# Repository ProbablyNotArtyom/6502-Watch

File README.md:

# 6502-Watch
6502 powered wearable with an LCD screen, keyboard interface, and compact form factor, all running ehBasic to boot.

<p align="center">
    <a href="https://hackaday.io/project/166496-65p-6502-powered-watch">(Link to this project's Hackaday.io page)</a>
    <br>
    <a href="https://blog.notartyoms-box.net/6502-watch">(Link this project's homepage on my website)</a>
</p>

### About

The 6502 has been around for just about 40 years, yet still powers the hearts of many electrical systems in place today, such as many microcontrollers and embedded systems. In fact, WDC still manufactures the 6502 and 65xx series chips under the 65c02 and 65cxx. I've noticed that WDC also introduced more package variants of the 6502 and 6522, such as PLCC and QFP. Another thing I noticed was the fact that these form factors of the 65c02 are almost never used. Given that the only people buying these are hobbyists, that isn't too suprizing, as they dont offer much over the standard 40 pin DIP.What they do offer, however, is small package size. I went off to try and design the smallest 6502 SBC i could, and was pleasantly suprized with the results. What I ended up with was what i think is the smallest hobbyist 6502 SBC produced. Small enough, in fact, that you could easily wear it on your wrist! I then added the neat little Nokia 5110 LCD and a cool interface, and now have what I believe to be the only 6502-driven watch in existance.

This repository contains all of the KiCad project files for the hardware, and all of the assembly sources for my software. To build the software you will need KickAssembler.

### Hardware

The watch is pretty standard as far as 6502 hardware goes:

 * 65c02 running @ 8MHz
 * 65c22 (controls LCD, keyboard, and buttons)
 * Nokia 5110 LCD (84x48)
 * 32k SRAM
 * 16k ROM
 * C64 Keyboard Connector

Probably the strangest bit there is the full size C64 keyboard connector along the top of the watch. I had wanted to have some form of keyboard input, but most options are entirely out of reach of the poor 6502. The only way i could come up with is to use a preexisting matrix keyboard; I happened to have a lot of unused commodore keyboards, so that's what ended up on there.

The part that ties everything together is really the tiny Nokia LCD. It's interfaced through SPI, which i had to bitbang through the 6522 VIA. The VIA also interfaces with the keyboard, and the face buttons. An interesting thing to note here is that the VIA only has 16 i/o pins, which in this case are all needed to interface just with the keyboard alone. I was able to use some of those pins for both the keyboard and the LCD without causing any sort of corruption with a bit of luck, and a lot more trial and error.

### Software

The watch has a few different things on its ROM. The primary thing is G'Mon, a machine monitor i wrote for the 6502. It  supports viewing memory in single and batch, depositing memory in single or batch, jumping to programs, filling blocks of memory with a pattern byte, and moving blocks of memory. I had to strip a few of the less useful commands out in order to fit it on the ROM with everything else. The secondary thing on there is Lee Davidson's Enhanced Basic. I was just barely able to fit into the ROM with everything else, like there are only around 100 bytes free. EhBasic has been modified to hook into the watch's main code, but other than that it's a completely normal version of EhBasic!

The thing that greets you when you start up the watch is the watch interface. Clever name, i know. It just provides a graphical menu you can move through to select what you want to run. This is the only place where the face buttons are actually used, at least on purpose. The topmost button is what brings up the menu. Interesting bit about that: its connected directly to the NMI pin on the 6502, so it can be used to get back to the watch menu from almost anywhere on the thing (unless you crash the 6502).

In my sources, there is a big blob of code that handles interfacing with the watch hardware; It's called the kernel there, but its less of a kernel and more of a library everything else references. Some of the more interesting things in there are the SPI bitbanging stuff for the LCD, and the matrix scanning and decoding routine for the keyboard.

Speaking of sources, they are all uploaded on here, of course. All the assembler code is written to be assembled using KickAssembler, and makes quite heavy use of its macro capabilities, so i doubt it would be fun to try and assemble with anything else. Here i have also included the EhBasic sources that i have modified; They have been modified to be assembled with KickAssembler. Everything builds at the same time, just run the ./Compile.sh script and it will spit out a ROM image. If for some reason you feel the need to fiddle with it, then make sure to go to Configuration.asm: That's the header that holds a bunch of the miscellaneous variables, like the location of the ROM in memory.

If you every wanted to run the software yourself, then you can do that as well. If you set the Emulated variable in the config file to true, then it will build a ROM for use with Symon.

### Other Software Toys

I have written a few extra programs to show what the hardware itself can do. The first thing is a little sprite demo that has 8 animated software sprites bouncing around the screen, plus a text scroller along the top. The visibility is quite poor with it, as the LCD sure does take its time with updating the pixels, which causes everything moving to be a little blurry. To combat this I had to wait a bit after each frame for the LCD to update, which means that the demo itself runs a little slower than it actually could on the hardware. A video of this demo in action is in the Demos section.

Did i mention it runs Tetris? Because yea, it sure does. I wrote a version of Tetris for the watch not long after realizing it was probably the only practical thing that it could feasibly do. Its a pretty standard Tetris clone, following pretty much all of the mechanics of the original versions. This means having the scoring system, having the progressive levels, all the tetrominoes, etc. Its controlled using the face buttons, using the navigation buttons as left & right, the center button as rotate, and the NMI button as the drop button. At the moment I don't have actual recordings of Tetris running on the watch, mostly because i am too lazy to do that much work for a project that was finished nearly 2 and a half years as of this write-up, but i do have the graphics assets i made for it, and have put them together into what it looks like while. If you don't believe that I wrote Tetris for it, then don't worry, just take a look at the sources that i have included with the project's main downloads.

### More Information

 * [My Website](http://notartyoms-box.net/6502watch.html)

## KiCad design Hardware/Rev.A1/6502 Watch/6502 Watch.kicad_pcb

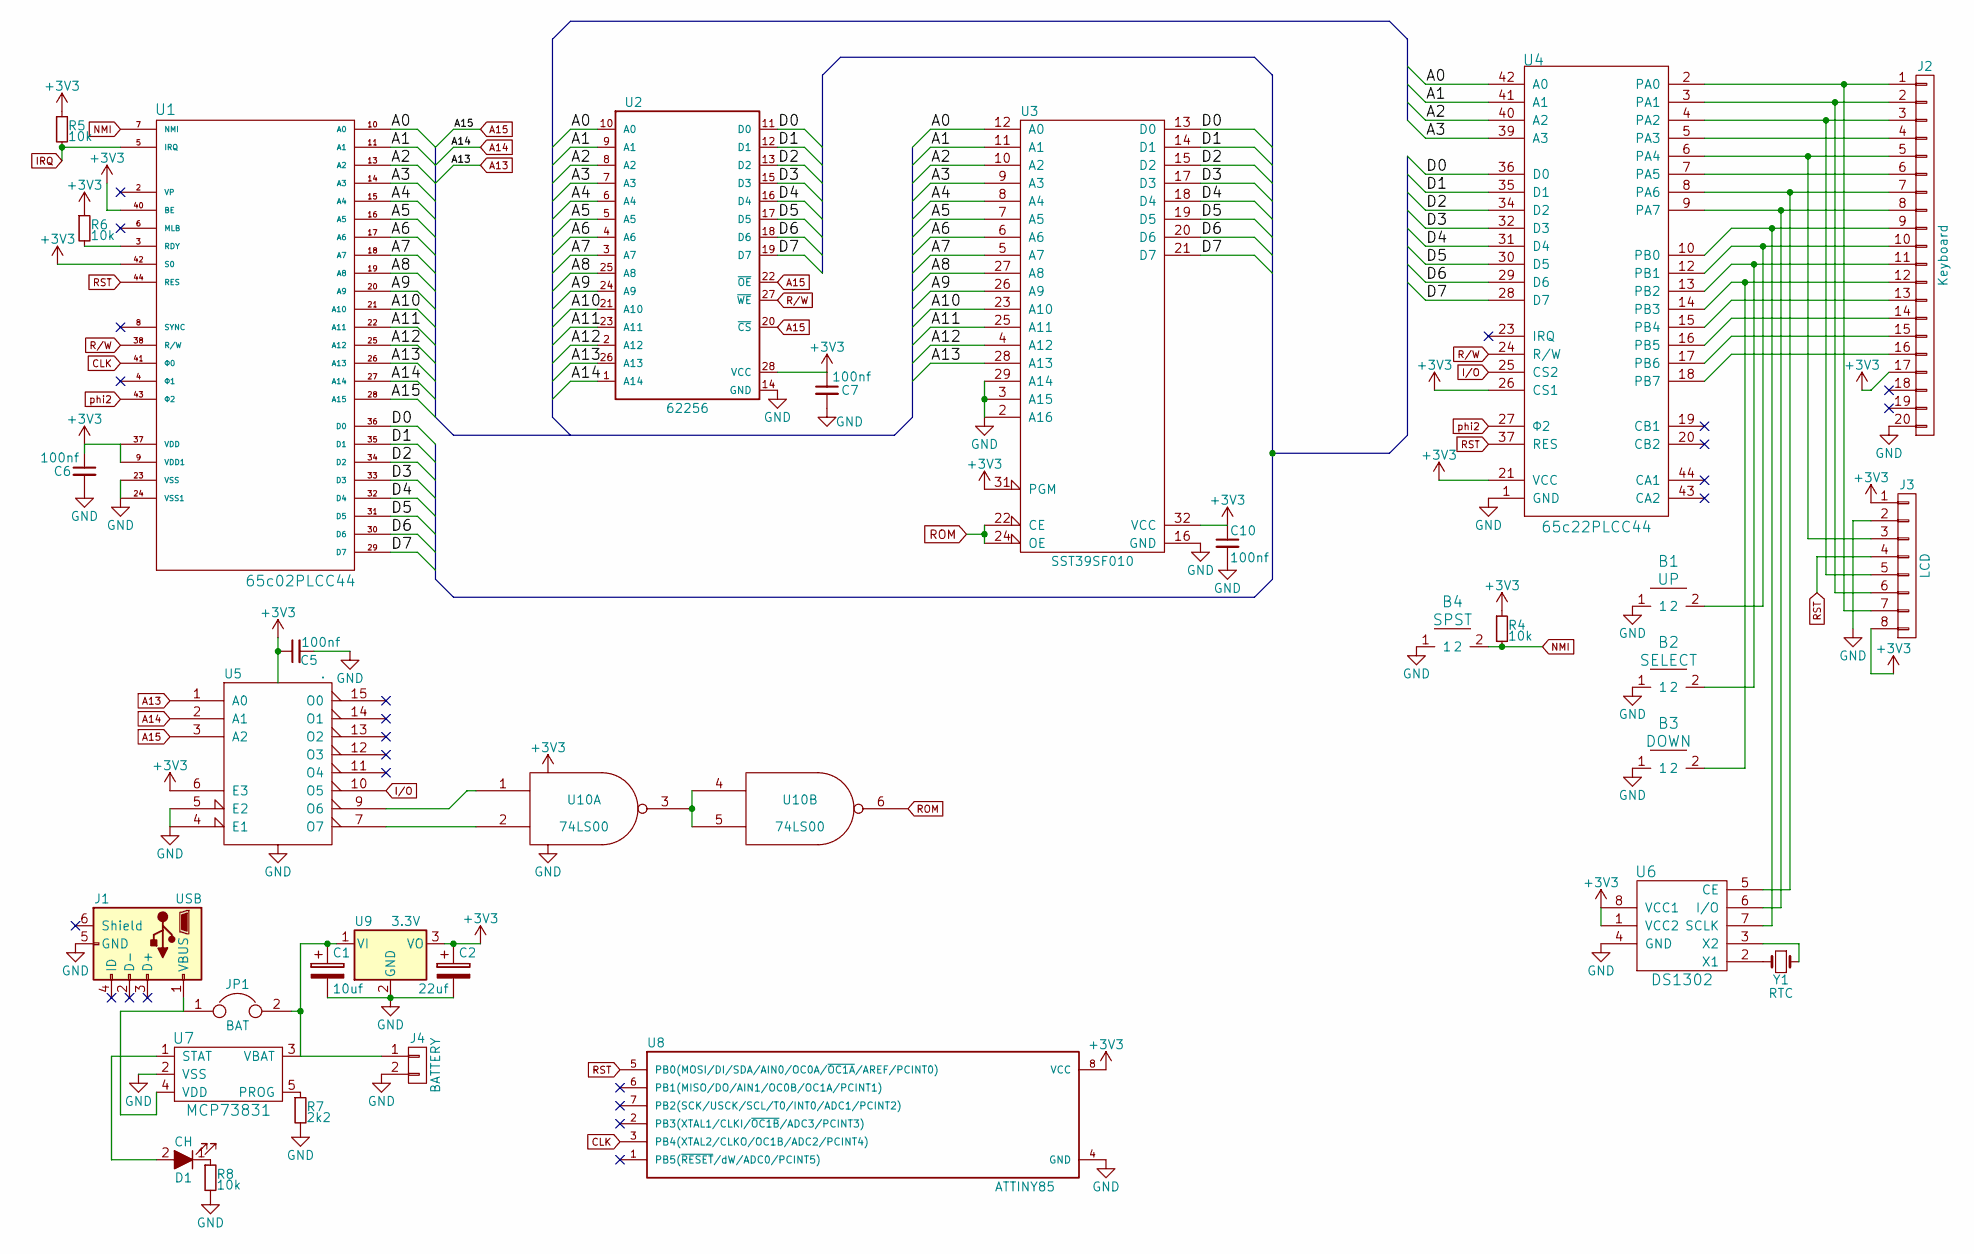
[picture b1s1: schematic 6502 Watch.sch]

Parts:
B1: UP; SW_SPST_B3S-1000(4P)
B2: SELECT; SW_SPST_B3S-1000(4P)
B3: DOWN; SW_SPST_B3S-1000(4P)
B4: SPST; SW_SPST_B3S-1000(4P)
C1: 10uf; C_1206_HandSoldering
C2: 22uf; C_1206_HandSoldering
C5, C6, C7, C10: 100nf; C_1210_HandSoldering
D1: CH; LED_1206
J1: USB; USB_Mini-B
J2: Keyboard; Pin_Header_Angled_1x20_Pitch2.54mm
J3: LCD; Pin_Header_Straight_1x08_Pitch2.54mm
J4: BATTERY; Pin_Header_Straight_1x02_Pitch2.54mm
JP1: BAT; R_0805_HandSoldering
R4, R5, R6, R8: 10k; R_1206_HandSoldering
R7: 2k2; R_1206_HandSoldering
U1: 65c02PLCC44; PLCC-44
U2: 62256; SOP-28_8.40x48mm_Pitch1.27mm
U3: SST39SF010; PLCC-32_THT-Socket_Fixed
U4: 65c22PLCC44; PLCC-44
U5: .; SOIC-16_3.9x9.9mm_Pitch1.27mm
U6: DS1302; SOIC-8_3.9x4.9mm_Pitch1.27mm
U7: MCP73831; SOT-23-5_HandSoldering
U8: ATTINY85; SOIC-8-N
U9: 3.3V; SOT-223-3Lead_TabPin2
U10: 74LS00; SOIC-14_3.9x8.7mm_Pitch1.27mm
Y1: RTC; Crystal_DS26_d2.0mm_l6.0mm_Horizontal

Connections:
+3V3: C2.1, C5.1, C6.1, C7.1, C10.1, J2.17, J3.1, J3.8, R4.1, R5.1, R6.1, U1.9 (VDD1), U1.37 (VDD), U1.40 (BE), U1.42 (S0), U2.28 (VCC), U3.31 (PGM), U3.32 (VCC), U4.21 (VCC), U4.26 (CS1), U5.6 (E3), U5.16 (VCC), U6.1 (VCC2), U6.8 (VCC1), U8.8 (VCC), U9.3 (VO), U10.14 (VCC)
/A0: U1.10 (A0), U2.10 (A0), U3.12 (A0), U4.42 (A0)
/A1: U1.11 (A1), U2.9 (A1), U3.11 (A1), U4.41 (A1)
/A2: U1.13 (A2), U2.8 (A2), U3.10 (A2), U4.40 (A2)
/A3: U1.14 (A3), U2.7 (A3), U3.9 (A3), U4.39 (A3)
/A4: U1.15 (A4), U2.6 (A4), U3.8 (A4)
/A5: U1.16 (A5), U2.5 (A5), U3.7 (A5)
/A6: U1.17 (A6), U2.4 (A6), U3.6 (A6)
/A7: U1.18 (A7), U2.3 (A7), U3.5 (A7)
/A8: U1.19 (A8), U2.25 (A8), U3.27 (A8)
/A9: U1.20 (A9), U2.24 (A9), U3.26 (A9)
/A10: U1.21 (A10), U2.21 (A10), U3.23 (A10)
/A11: U1.22 (A11), U2.23 (A11), U3.25 (A11)
/A12: U1.25 (A12), U2.2 (A12), U3.4 (A12)
/D0: U1.36 (D0), U2.11 (D0), U3.13 (D0), U4.36 (D0)
/D1: U1.35 (D1), U2.12 (D1), U3.14 (D1), U4.35 (D1)
/D2: U1.34 (D2), U2.13 (D2), U3.15 (D2), U4.34 (D2)
/D3: U1.33 (D3), U2.15 (D3), U3.17 (D3), U4.32 (D3)
/D4: U1.32 (D4), U2.16 (D4), U3.18 (D4), U4.31 (D4)
/D5: U1.31 (D5), U2.17 (D5), U3.19 (D5), U4.30 (D5)
/D6: U1.30 (D6), U2.18 (D6), U3.20 (D6), U4.29 (D6)
/D7: U1.29 (D7), U2.19 (D7), U3.21 (D7), U4.28 (D7)
A13: U1.26 (A13), U2.26 (A13), U3.28 (A13), U5.1 (A0)
A14: U1.27 (A14), U2.1 (A14), U5.2 (A1)
A15: U1.28 (A15), U2.20 (~CS), U2.22 (~OE), U5.3 (A2)
CLK: U1.41 (Φ0), U8.3 (PB4(XTAL2/CLKO/OC1B/ADC2/PCINT4))
GND: B1.1, B2.1, B3.1, B4.1, C1.2, C2.2, C5.2, C6.2, C7.2, C10.2, J1.5 (GND), J2.20, J3.2, J4.2, R7.2, R8.2, U1.23 (VSS), U1.24 (VSS1), U2.14 (GND), U3.2 (A16), U3.3 (A15), U3.16 (GND), U3.29 (A14), U4.1 (GND), U5.4 (E1), U5.5 (E2), U5.8 (GND), U6.4 (GND), U7.2 (VSS), U8.4 (GND), U9.2 (GND), U10.7 (GND)
I/O: U4.25 (CS2), U5.10 (O5)
IRQ: R5.2, U1.5 (IRQ)
NMI: B4.2, B4.4, R4.2, U1.7 (NMI)
unnamed: B1.2, J2.10, U4.12 (PB1)
unnamed: B2.2, J2.11, U4.13 (PB2)
unnamed: B3.2, J2.12, U4.14 (PB3)
unnamed: C1.1, J4.1, JP1.2, U7.3 (VBAT), U9.1 (VI)
unnamed: D1.1 (K), R8.1
unnamed: D1.2 (A), U7.1 (STAT)
unnamed: J1.1 (VBUS), JP1.1, U7.4 (VDD)
unnamed: J2.1, J3.7, U4.2 (PA0)
unnamed: J2.2, J3.6, U4.3 (PA1)
unnamed: J2.3, J3.5, U4.4 (PA2)
unnamed: J2.4, U4.5 (PA3)
unnamed: J2.5, J3.3, U4.6 (PA4)
unnamed: J2.6, U4.7 (PA5)
unnamed: J2.7, U4.8 (PA6), U6.5 (CE)
unnamed: J2.8, U4.9 (PA7), U6.6 (I/O)
unnamed: J2.9, U4.10 (PB0), U6.7 (SCLK)
unnamed: J2.13, U4.15 (PB4)
unnamed: J2.14, U4.16 (PB5)
unnamed: J2.15, U4.17 (PB6)
unnamed: J2.16, U4.18 (PB7)
unnamed: R6.2, U1.3 (RDY)
unnamed: R7.1, U7.5 (PROG)
unnamed: U6.2 (X1), Y1.2
unnamed: U6.3 (X2), Y1.1
unnamed: U5.9 (O6), U10.1
unnamed: U5.7 (O7), U10.2
unnamed: U10.3, U10.4, U10.5
R/W: U1.38 (R/W), U2.27 (~WE), U4.24 (R/W)
ROM: U3.22 (CE), U3.24 (OE), U10.6
RST: J3.4, U1.44 (RES), U4.37 (RES), U8.5 (PB0(MOSI/DI/SDA/AIN0/OC0A/~OC1A~/AREF/P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)
phi2: U1.43 (Φ2), U4.27 (Φ2)

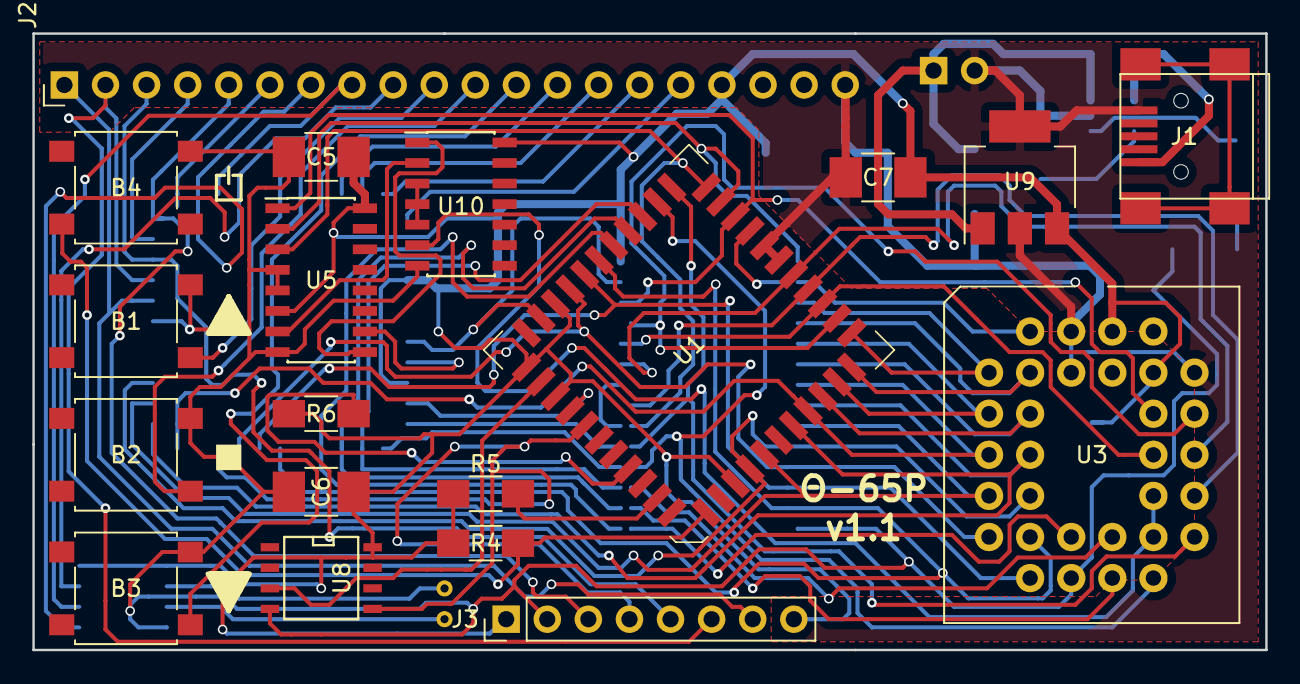
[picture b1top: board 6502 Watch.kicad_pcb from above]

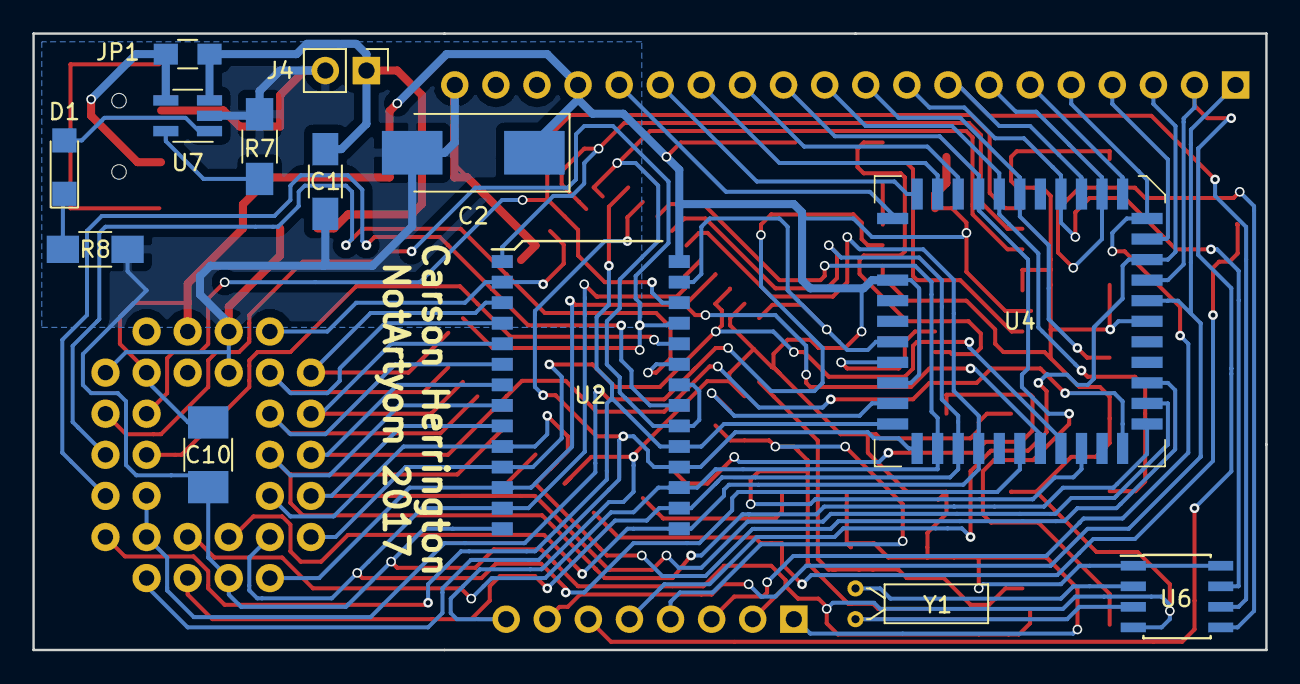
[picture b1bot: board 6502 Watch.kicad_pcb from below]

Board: 2 copper layers, 76.2 x 38.1 mm, 32 parts (13 on the bottom side), 61 nets.
